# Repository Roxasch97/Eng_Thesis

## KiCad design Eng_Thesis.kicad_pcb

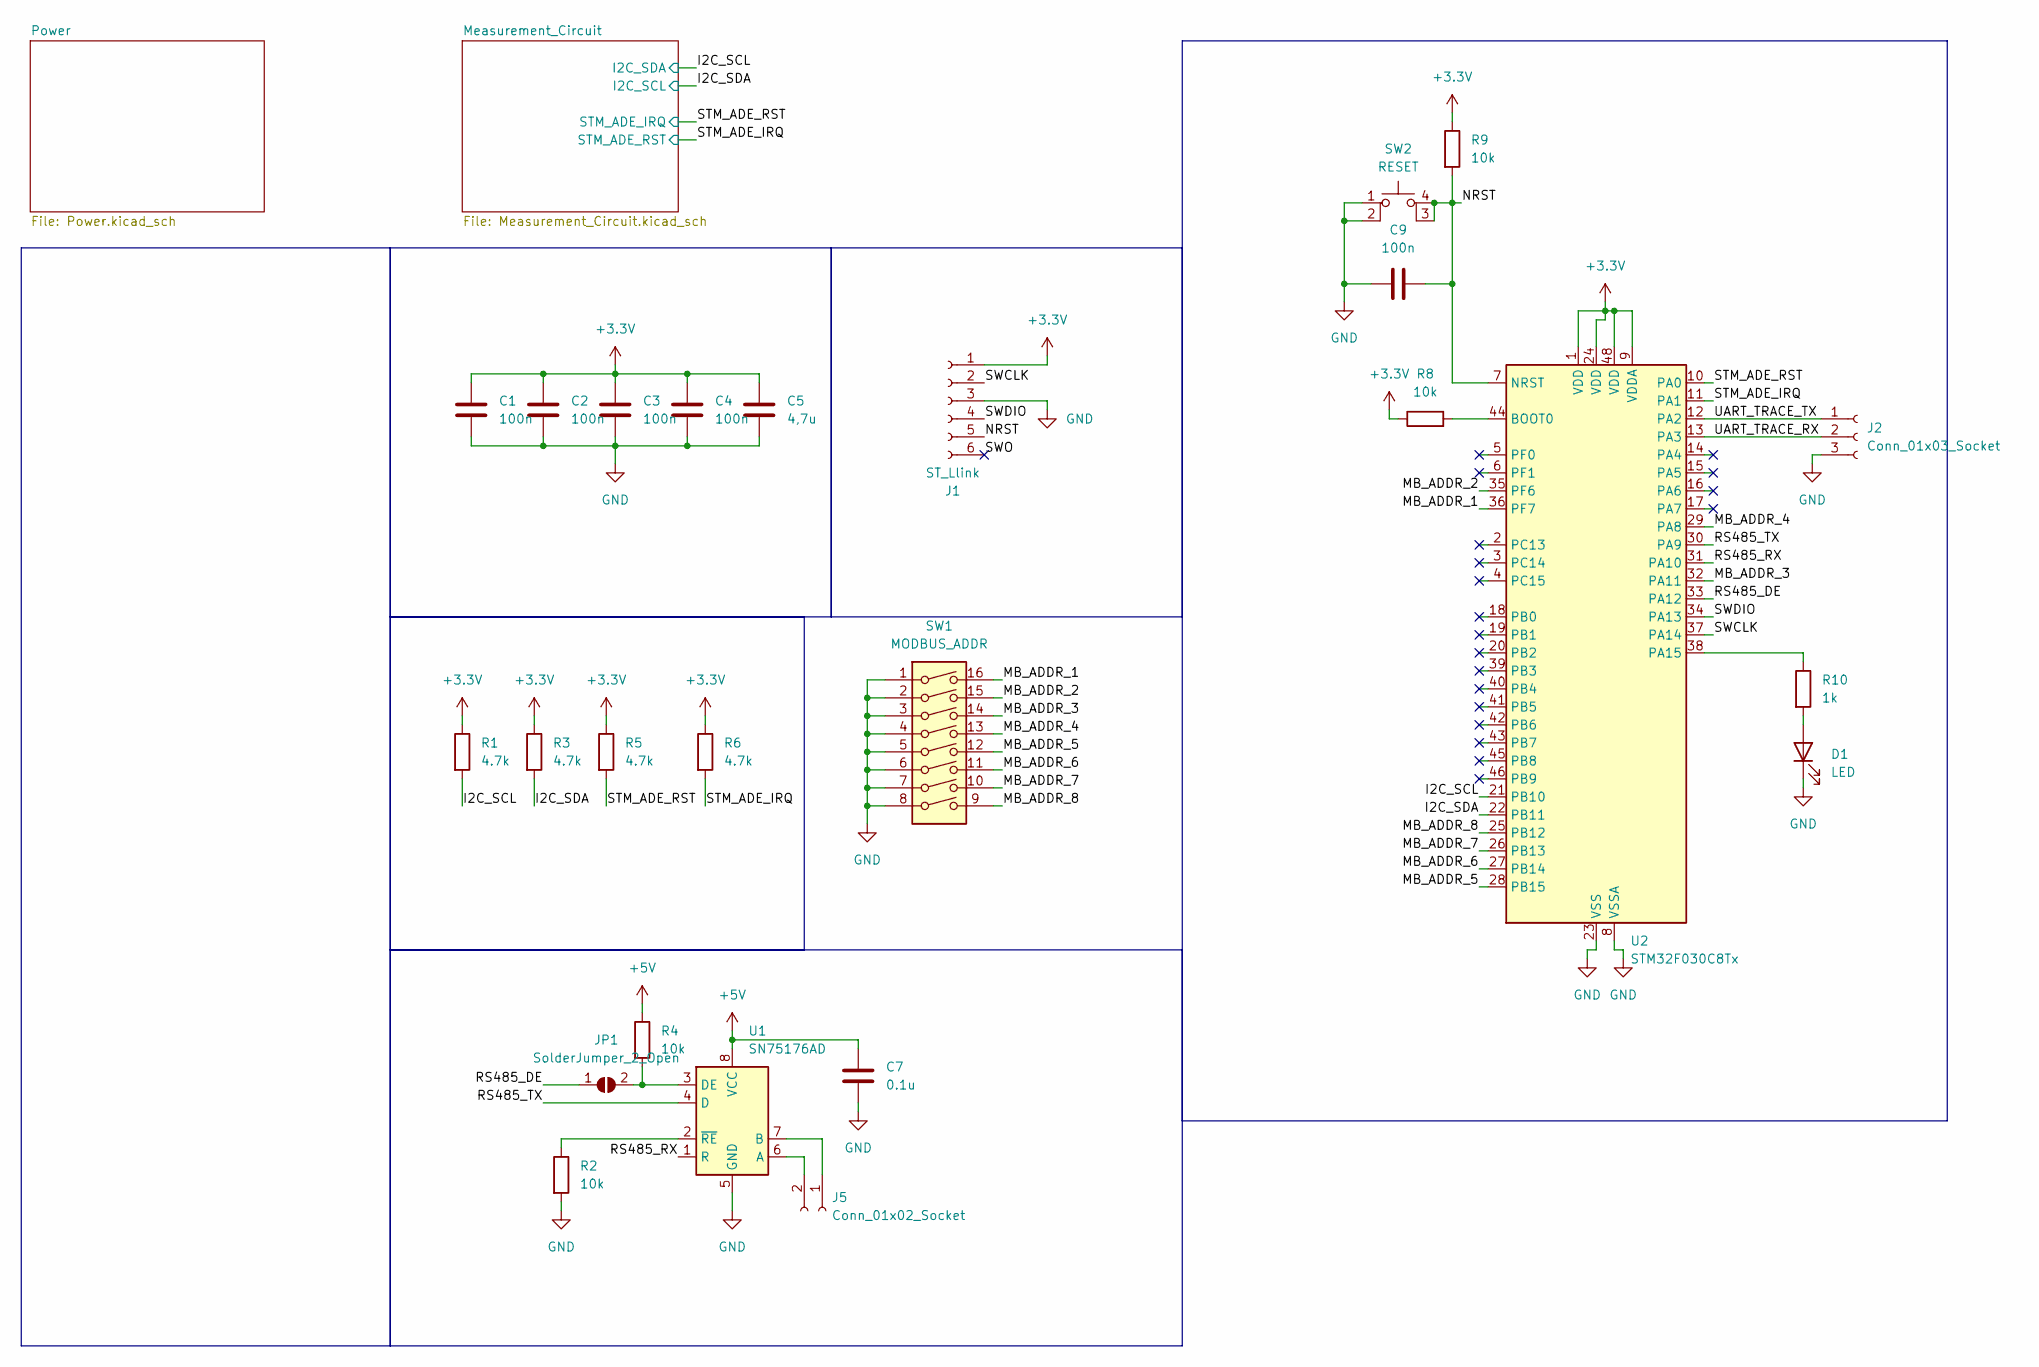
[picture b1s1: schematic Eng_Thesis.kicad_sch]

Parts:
C1, C2, C3, C4, C9: 100n; C_0805_2012Metric_Pad1.18x1.45mm_HandSolder
C5: 4,7u; C_0805_2012Metric_Pad1.18x1.45mm_HandSolder
C7: 0.1u; C_0805_2012Metric_Pad1.18x1.45mm_HandSolder
D1: LED; LED_0603_1608Metric_Pad1.05x0.95mm_HandSolder
J1: ST_Llink; PinHeader_1x06_P2.54mm_Vertical
J2: Conn_01x03_Socket; PinSocket_1x03_P2.54mm_Vertical
J5: Conn_01x02_Socket; TB508P2PBL
JP1: SolderJumper_2_Open; SolderJumper-2_P1.3mm_Open_TrianglePad1.0x1.5mm
R1, R3, R5, R6: 4.7k; R_0805_2012Metric_Pad1.20x1.40mm_HandSolder
R2, R4, R8, R9: 10k; R_0805_2012Metric_Pad1.20x1.40mm_HandSolder
R10: 1k; R_0805_2012Metric_Pad1.20x1.40mm_HandSolder
SW1: MODBUS_ADDR; SDA08H1BD
SW2: RESET; TL3305BF160QG
U1: SN75176AD; SOIC-8_3.9x4.9mm_P1.27mm
U2: STM32F030C8Tx; LQFP-48_7x7mm_P0.5mm

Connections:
+3.3V: C1.1, C2.1, C3.1, C4.1, C5.1, J1.1, R1.1, R3.1, R5.1, R6.1, R8.1, R9.1, U2.1 (VDD), U2.9 (VDDA), U2.24 (VDD), U2.48 (VDD); also elsewhere on the board
+5V: C7.1, R4.1, U1.8 (VCC); also elsewhere on the board
/I2C_SCL: R1.2, U2.21 (PB10); also elsewhere on the board
/I2C_SDA: R3.2, U2.22 (PB11); also elsewhere on the board
/MB_ADDR_1: SW1.16, U2.36 (PF7)
/MB_ADDR_2: SW1.15, U2.35 (PF6)
/MB_ADDR_3: SW1.14, U2.32 (PA11)
/MB_ADDR_4: SW1.13, U2.29 (PA8)
/MB_ADDR_5: SW1.12, U2.28 (PB15)
/MB_ADDR_6: SW1.11, U2.27 (PB14)
/MB_ADDR_7: SW1.10, U2.26 (PB13)
/MB_ADDR_8: SW1.9, U2.25 (PB12)
/NRST: C9.2, J1.5, R9.2, SW2.3 (K), SW2.4 (A), U2.7 (NRST)
/RS485_DE: JP1.1 (A), U2.33 (PA12)
/RS485_RX: U1.1 (R), U2.31 (PA10)
/RS485_TX: U1.4 (D), U2.30 (PA9)
/STM_ADE_IRQ: R6.2, U2.11 (PA1); also elsewhere on the board
/STM_ADE_RST: R5.2, U2.10 (PA0); also elsewhere on the board
/SWCLK: J1.2, U2.37 (PA14)
/SWDIO: J1.4, U2.34 (PA13)
/SWO: J1.6
/UART_TRACE_RX: J2.2, U2.13 (PA3)
/UART_TRACE_TX: J2.1, U2.12 (PA2)
GND: C1.2, C2.2, C3.2, C4.2, C5.2, C7.2, C9.1, D1.1 (K), J1.3, J2.3, R2.2, SW1.1, SW1.2, SW1.3, SW1.4, SW1.5, SW1.6, SW1.7, SW1.8, SW2.1, SW2.2, U1.5 (GND), U2.8 (VSSA), U2.23 (VSS), U2.47 (VSS); also elsewhere on the board
unnamed: D1.2 (A), R10.2
unnamed: J5.1, U1.7 (B)
unnamed: J5.2, U1.6 (A)
unnamed: JP1.2 (B), R4.2, U1.3 (DE)
unnamed: R2.1, U1.2 (~RE)
unnamed: R8.2, U2.44 (BOOT0)
unnamed: R10.1, U2.38 (PA15)

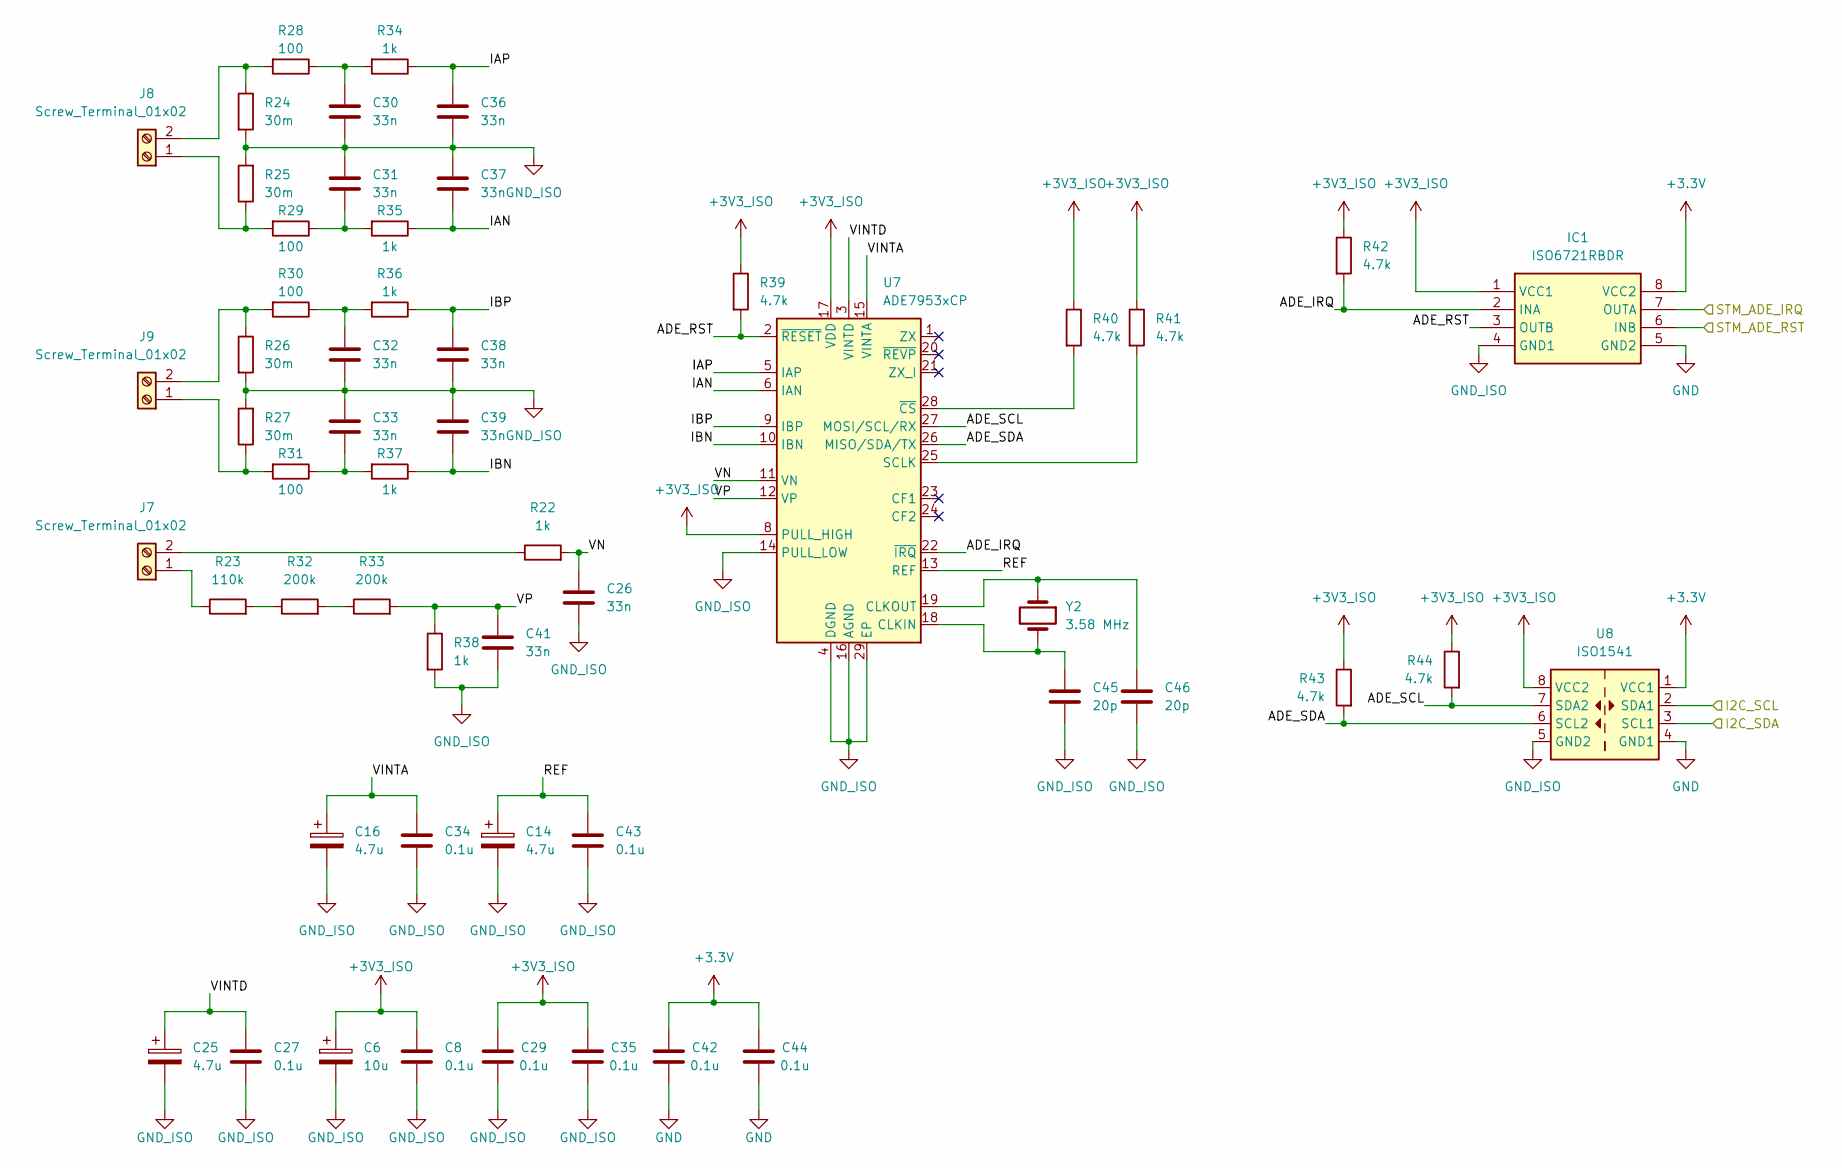
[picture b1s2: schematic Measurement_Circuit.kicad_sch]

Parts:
C6: 10u; CP_EIA-3216-18_Kemet-A_Pad1.58x1.35mm_HandSolder
C8, C27, C29, C34, C35, C42, C43, C44: 0.1u; C_0805_2012Metric_Pad1.18x1.45mm_HandSolder
C14, C16, C25: 4.7u; CP_EIA-3216-18_Kemet-A_Pad1.58x1.35mm_HandSolder
C26, C30, C31, C32, C33, C36, C37, C38, C39: 33n; C_0805_2012Metric_Pad1.18x1.45mm_HandSolder
C41: 33n; C_1210_3225Metric_Pad1.33x2.70mm_HandSolder
C45, C46: 20p; C_0805_2012Metric_Pad1.18x1.45mm_HandSolder
IC1: ISO6721RBDR; SOIC127P600X175-8N; Mouser Part Number 595-ISO6721RBDR
J7, J8, J9: Screw_Terminal_01x02; TB508P2PBL
R22, R34, R35, R36, R37, R38: 1k; R_0805_2012Metric_Pad1.20x1.40mm_HandSolder
R23: 110k; R_0805_2012Metric_Pad1.20x1.40mm_HandSolder
R24, R25, R26, R27: 30m; R_2512_6332Metric_Pad1.40x3.35mm_HandSolder
R28, R29, R30, R31: 100; R_0805_2012Metric_Pad1.20x1.40mm_HandSolder
R32, R33: 200k; R_0805_2012Metric_Pad1.20x1.40mm_HandSolder
R39, R40, R41, R42, R43, R44: 4.7k; R_0805_2012Metric_Pad1.20x1.40mm_HandSolder
U7: ADE7953xCP; LFCSP-28-1EP_5x5mm_P0.5mm_EP3.14x3.14mm
U8: ISO1541; SOIC-8_3.9x4.9mm_P1.27mm
Y2: 3.58 MHz; Crystal_SMD_HC49-SD_HandSoldering

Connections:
+3.3V: C42.2, C44.2, IC1.8 (VCC2), U8.1 (VCC1); also elsewhere on the board
+3V3_ISO: C6.1, C8.1, C29.2, C35.2, IC1.1 (VCC1), R39.1, R40.1, R41.1, R42.1, R43.1, R44.1, U7.7 (PULL_HIGH), U7.8 (PULL_HIGH), U7.17 (VDD), U8.8 (VCC2); also elsewhere on the board
/I2C_SCL: U8.3 (SCL1); also elsewhere on the board
/I2C_SDA: U8.2 (SDA1); also elsewhere on the board
/Measurement_Circuit/ADE_IRQ: IC1.2 (INA), R42.2, U7.22 (~IRQ)
/Measurement_Circuit/ADE_RST: IC1.3 (OUTB), R39.2, U7.2 (~RESET)
/Measurement_Circuit/ADE_SCL: R44.2, U7.27 (MOSI/SCL/RX), U8.7 (SDA2)
/Measurement_Circuit/ADE_SDA: R43.2, U7.26 (MISO/SDA/TX), U8.6 (SCL2)
/Measurement_Circuit/IAN: C37.2, R35.1, U7.6 (IAN)
/Measurement_Circuit/IAP: C36.1, R34.1, U7.5 (IAP)
/Measurement_Circuit/IBN: C39.2, R37.1, U7.10 (IBN)
/Measurement_Circuit/IBP: C38.1, R36.1, U7.9 (IBP)
/Measurement_Circuit/REF: C14.1, C43.1, U7.13 (REF)
/Measurement_Circuit/VINTA: C16.1, C34.1, U7.15 (VINTA)
/Measurement_Circuit/VINTD: C25.1, C27.1, U7.3 (VINTD)
/Measurement_Circuit/VN: C26.1, R22.2, U7.11 (VN)
/Measurement_Circuit/VP: C41.1, R33.2, R38.1, U7.12 (VP)
/STM_ADE_IRQ: IC1.6 (INB); also elsewhere on the board
/STM_ADE_RST: IC1.7 (OUTA); also elsewhere on the board
GND: C42.1, C44.1, IC1.5 (GND2), U8.4 (GND1); also elsewhere on the board
GND_ISO: C6.2, C8.2, C14.2, C16.2, C25.2, C26.2, C27.2, C29.1, C30.2, C31.1, C32.2, C33.1, C34.2, C35.1, C36.2, C37.1, C38.2, C39.1, C41.2, C43.2, C45.2, C46.2, IC1.4 (GND1), R24.2, R25.2, R26.2, R27.2, R38.2, U7.4 (DGND), U7.14 (PULL_LOW), U7.16 (AGND), U7.29 (EP), U8.5 (GND2); also elsewhere on the board
unnamed: C30.1, R28.1, R34.2
unnamed: C31.2, R29.1, R35.2
unnamed: C32.1, R30.1, R36.2
unnamed: C33.2, R31.1, R37.2
unnamed: J7.1, R23.1
unnamed: J7.2, R22.1
unnamed: J8.1, R25.1, R29.2
unnamed: J8.2, R24.1, R28.2
unnamed: J9.1, R27.1, R31.2
unnamed: J9.2, R26.1, R30.2
unnamed: R23.2, R32.1
unnamed: R32.2, R33.1
unnamed: C45.1, U7.18 (CLKIN), Y2.2
unnamed: C46.1, U7.19 (CLKOUT), Y2.1
unnamed: R41.2, U7.25 (SCLK)
unnamed: R40.2, U7.28 (~CS)

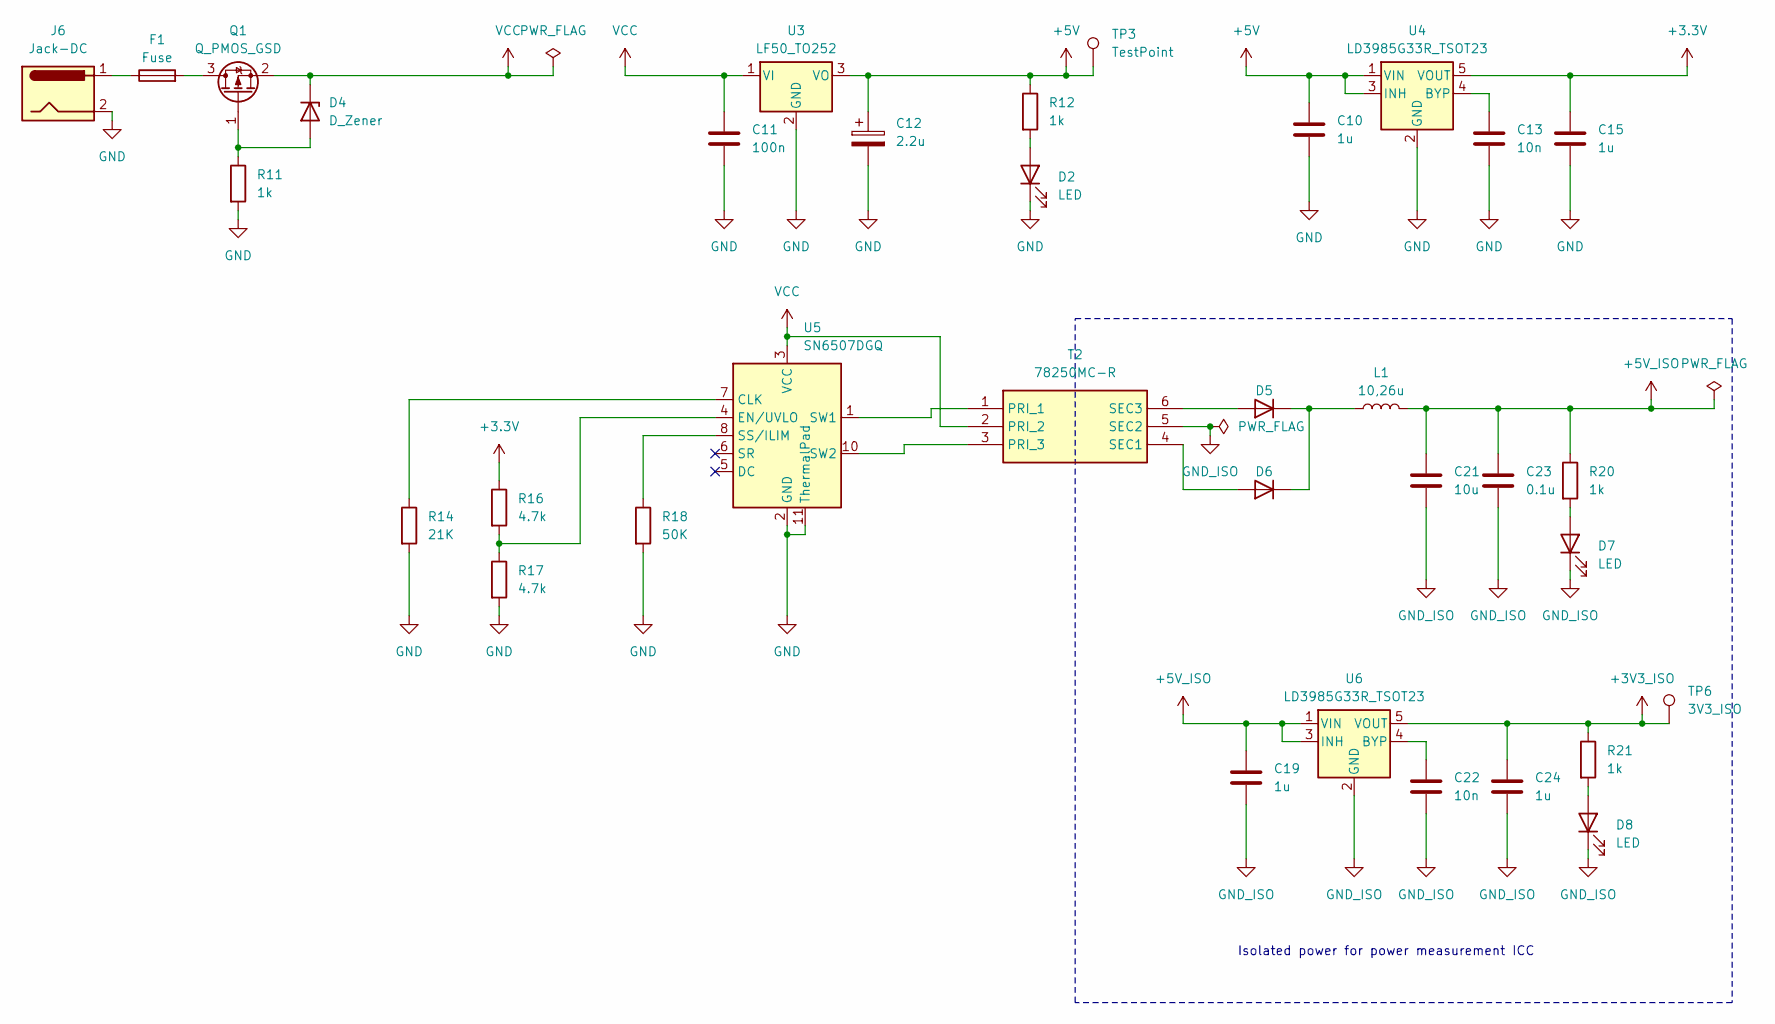
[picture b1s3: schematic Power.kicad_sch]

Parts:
C10, C15, C19, C24: 1u; C_0805_2012Metric_Pad1.18x1.45mm_HandSolder
C11: 100n; C_0805_2012Metric_Pad1.18x1.45mm_HandSolder
C12: 2.2u; CP_Elec_4x5.3
C13, C22: 10n; C_0805_2012Metric_Pad1.18x1.45mm_HandSolder
C21: 10u; C_0805_2012Metric_Pad1.18x1.45mm_HandSolder
C23: 0.1u; C_0805_2012Metric_Pad1.18x1.45mm_HandSolder
D2, D7, D8: LED; LED_0603_1608Metric_Pad1.05x0.95mm_HandSolder
D4: D_Zener; D_MELF
D5, D6: BAT165E6327HTSA1; D_SOD-323F
F1: Fuse; Fuse_2920_7451Metric_Pad2.10x5.45mm_HandSolder
J6: Jack-DC; PCGK21
L1: 10,26u; L_1210_3225Metric_Pad1.42x2.65mm_HandSolder
Q1: Q_PMOS_GSD; SOT-23_Handsoldering
R11, R12, R20, R21: 1k; R_0805_2012Metric_Pad1.20x1.40mm_HandSolder
R14: 21K; R_0805_2012Metric_Pad1.20x1.40mm_HandSolder
R16, R17: 4.7k; R_0805_2012Metric_Pad1.20x1.40mm_HandSolder
R18: 50K; R_0805_2012Metric_Pad1.20x1.40mm_HandSolder
T2: 78250MC-R; SOP254P1270X660-6N; Mouser Part Number 580-78250MC-R
TP3: TestPoint; TestPoint_Pad_1.5x1.5mm
TP6: 3V3_ISO; TestPoint_Pad_1.5x1.5mm
U3: LF50_TO252; TO-252-2
U4, U6: LD3985G33R_TSOT23; TSOT-23-5
U5: SN6507DGQ; HVSSOP-10-1EP_3x3mm_P0.5mm_EP1.57x1.88mm

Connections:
+3.3V: C15.1, R16.1, U4.5 (VOUT); also elsewhere on the board
+3V3_ISO: C24.1, R21.1, TP6.1, U6.5 (VOUT); also elsewhere on the board
+5V: C10.1, C12.1, R12.1, TP3.1, U3.3 (VO), U4.1 (VIN), U4.3 (INH); also elsewhere on the board
+5V_ISO: C19.1, C21.1, C23.1, L1.2, R20.1, U6.1 (VIN), U6.3 (INH)
GND: C10.2, C11.2, C12.2, C13.2, C15.2, D2.1 (K), J6.2, R11.2, R14.2, R17.2, R18.2, U3.2 (GND), U4.2 (GND), U5.2 (GND), U5.9 (GND), U5.11 (ThermalPad); also elsewhere on the board
GND_ISO: C19.2, C21.2, C22.2, C23.2, C24.2, D7.1 (K), D8.1 (K), T2.5 (SEC2), U6.2 (GND); also elsewhere on the board
unnamed: D2.2 (A), R12.2
unnamed: D4.2 (A), Q1.1 (G), R11.1
unnamed: D5.2 (A), T2.6 (SEC3)
unnamed: D5.1 (K), D6.1 (K), L1.1
unnamed: D6.2 (A), T2.4 (SEC1)
unnamed: D7.2 (A), R20.2
unnamed: D8.2 (A), R21.2
unnamed: F1.1, J6.1
unnamed: F1.2, Q1.3 (D)
unnamed: T2.1 (PRI_1), U5.1 (SW1)
unnamed: T2.3 (PRI_3), U5.10 (SW2)
unnamed: C13.1, U4.4 (BYP)
unnamed: R14.1, U5.7 (CLK)
unnamed: R16.2, R17.1, U5.4 (EN/UVLO)
unnamed: R18.1, U5.8 (SS/ILIM)
unnamed: C22.1, U6.4 (BYP)
VCC: C11.1, D4.1 (K), Q1.2 (S), T2.2 (PRI_2), U3.1 (VI), U5.3 (VCC)

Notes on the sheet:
Isolated power for power measurement ICC

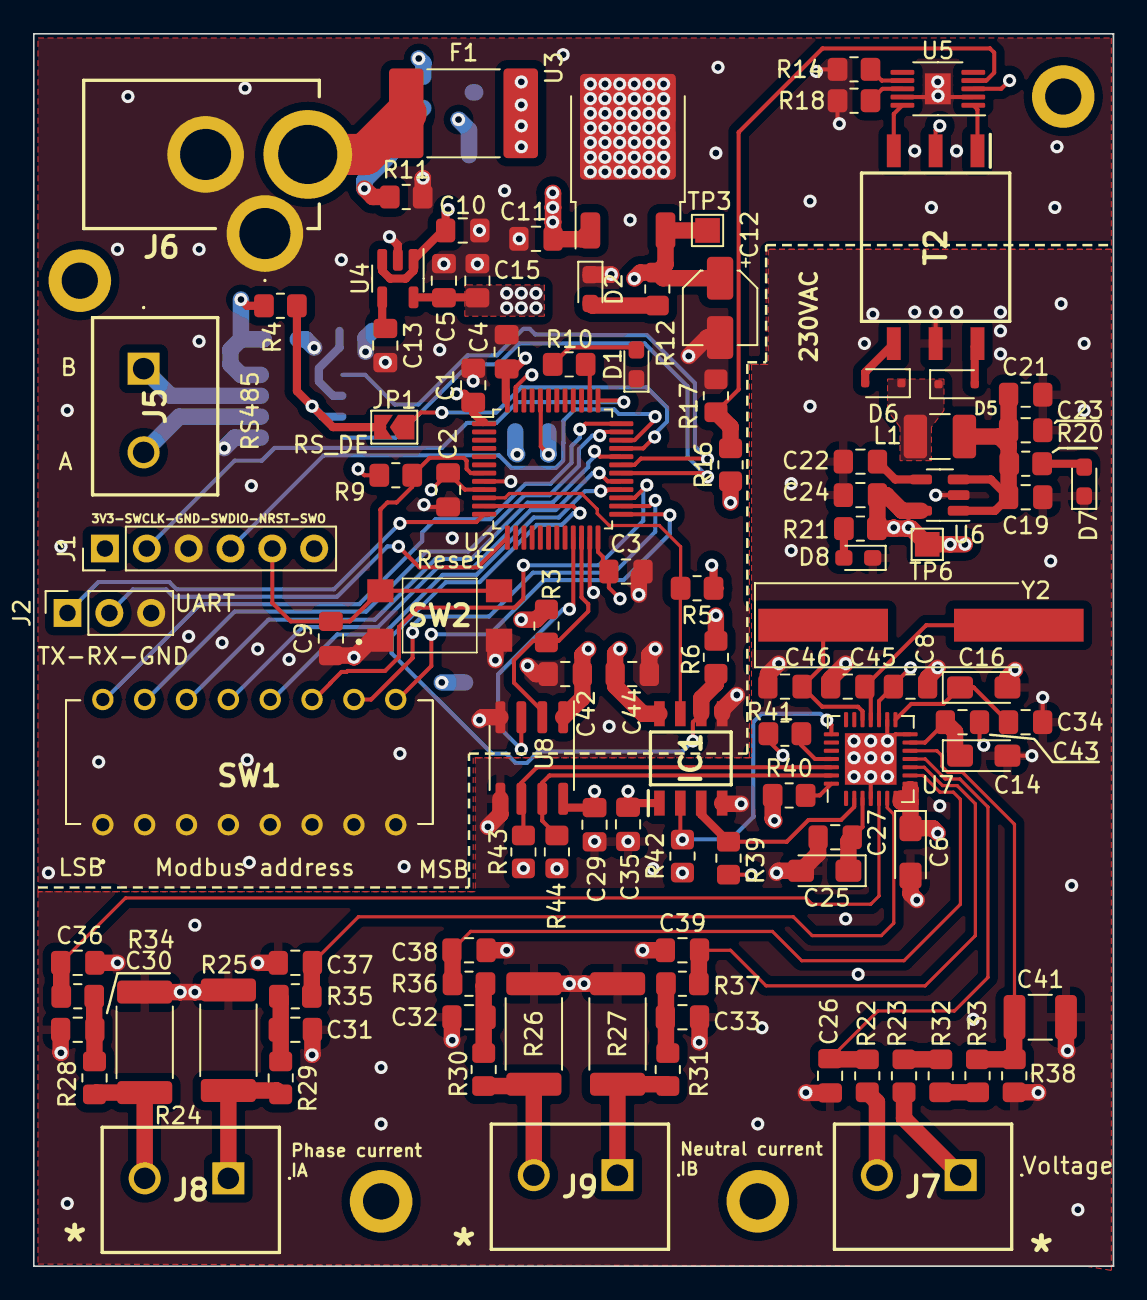
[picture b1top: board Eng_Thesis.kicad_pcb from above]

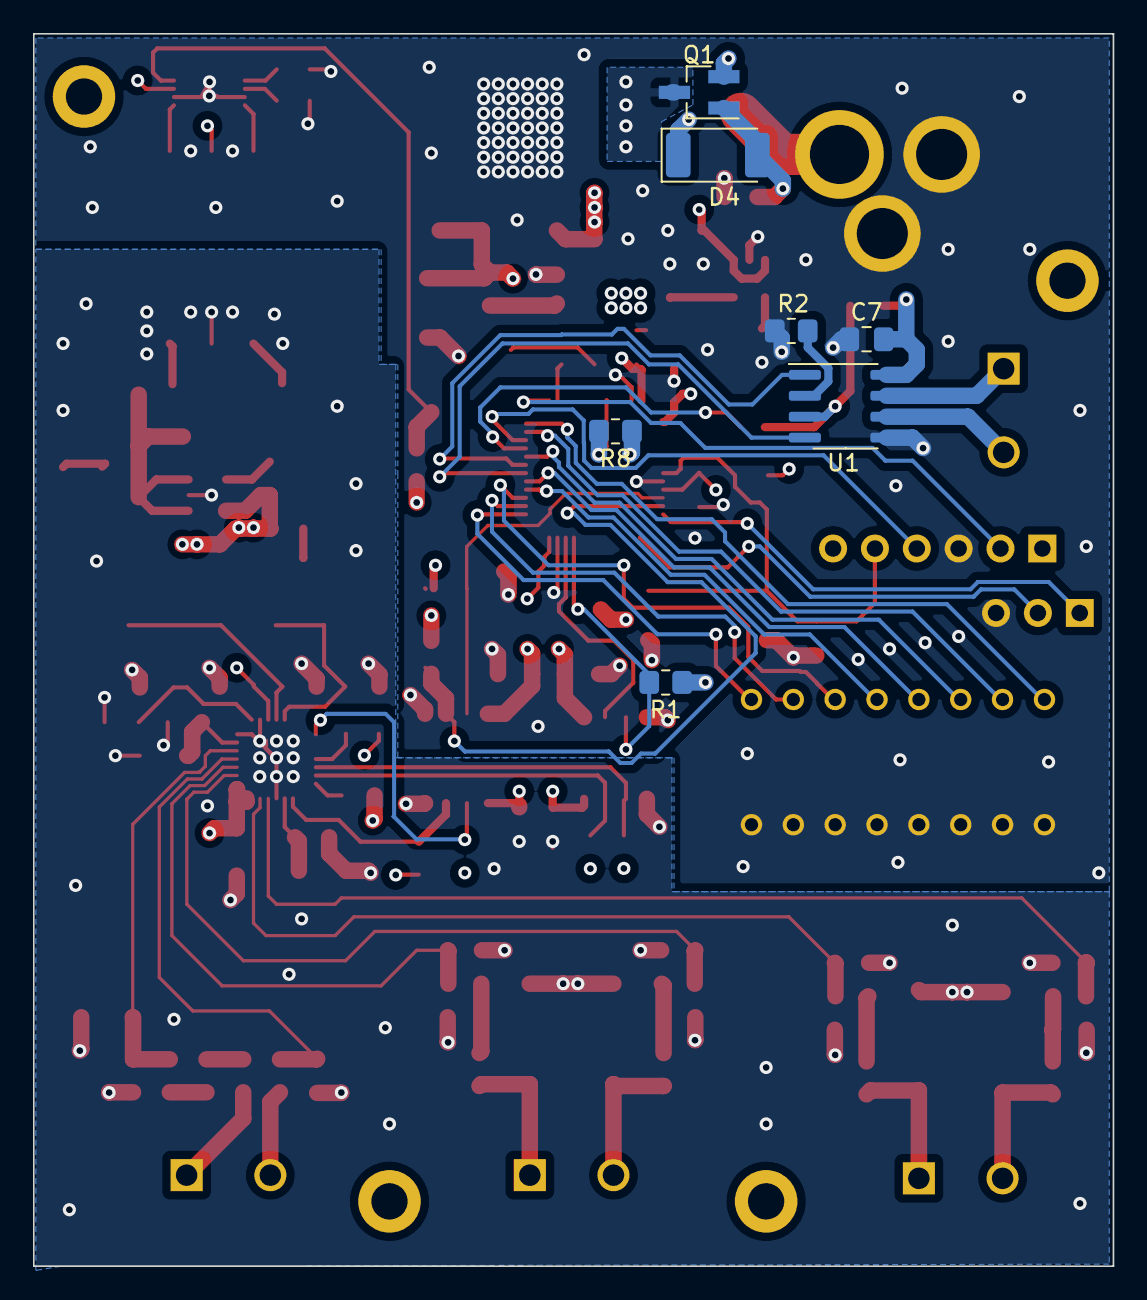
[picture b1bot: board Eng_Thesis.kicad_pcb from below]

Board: 4 copper layers, 65.5 x 74.8 mm, 114 parts (7 on the bottom side), 79 nets.

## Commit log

2023-10-30 Initial commit
    Initial commit with first draft of power section
2023-11-02 Power update - DC/DC Converter
    Updated the power source to be done on the DC/DC Converter
2023-11-04 Microcontroller draft
    Created a draft of the things connected to the microcontroller.
2023-11-13 Partial measurement block
    Added capacitor in Power, fixed the debug junction, added initial draft of measurement block
2024-03-21 Progress in measurement + rework of power
    Progressed in measurement circuit, and reworked the power supply to be isolated
2024-04-13 Filter values + isolation draft
2024-04-13 I2C pullups
2024-05-11 v0.1 of schematic + most of footprints/links
2024-06-07 Footprints and elements update
    Added another batch of footprints and links to the elements. More coming soon.
2024-07-15 1st complete version of schematic with footprints
2024-08-20 Fixes on schematics and footprint update
2024-10-16 v.0.1
